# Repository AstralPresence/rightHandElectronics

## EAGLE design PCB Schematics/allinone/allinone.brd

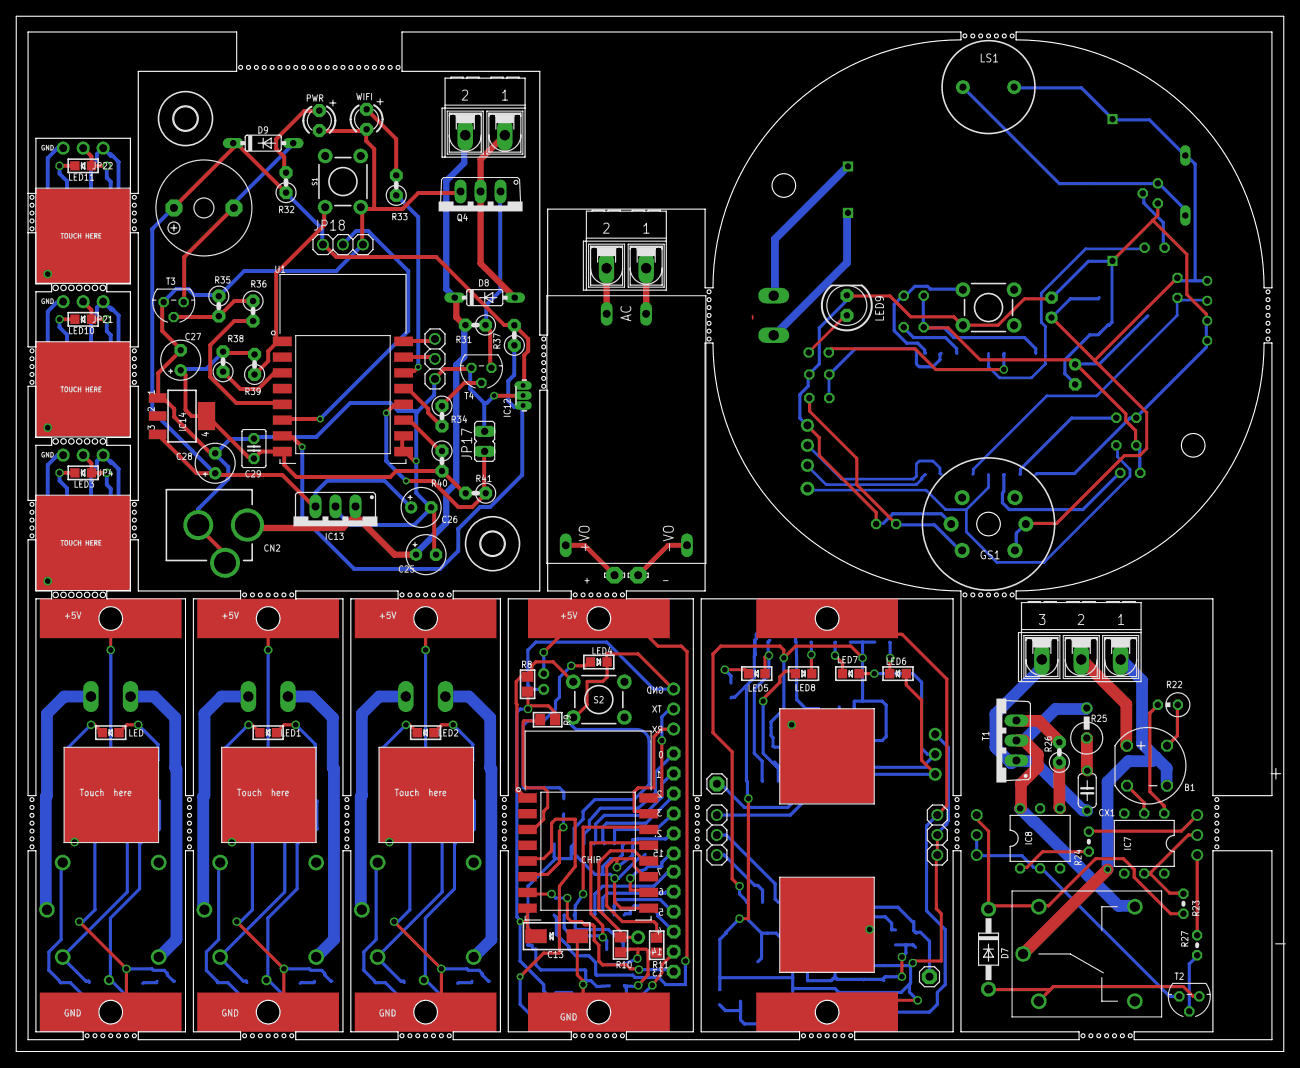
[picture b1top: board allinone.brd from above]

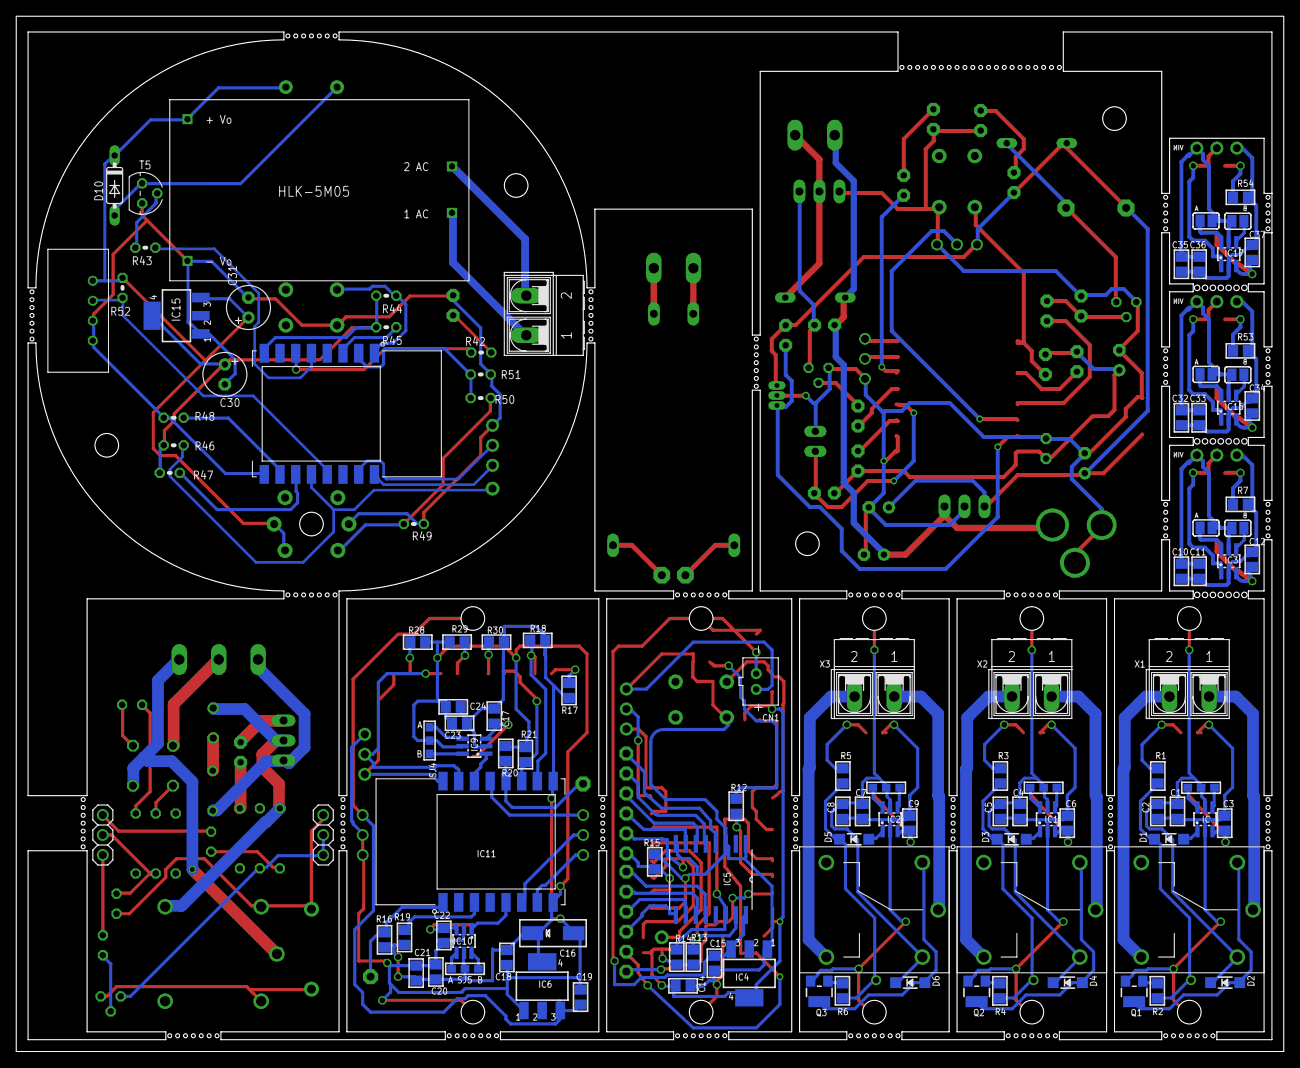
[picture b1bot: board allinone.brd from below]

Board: 2 copper layers, 161.0 x 131.5 mm, 224 parts (117 on the bottom side), 170 nets.

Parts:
AC: AK500/2-H
B1: W04/6/8/10; RB1A
C1, C4, C7, C10, C20, C23, C32, C35: 10uf; 0805
C2, C5, C8, C11, C21, C24, C33, C36: 0.1uf; 0805
C3, C6, C9, C17, C22: 50pF; 0805
C12, C34, C37: 50pf; 0805
C13, C16: 100UF; EIA6032-28/C-W
C14, C15: 0805
C18, C19: 10uF; 0805
C25, C26, C27, C28: E2,5-5
C29: C025-030X050
C30, C31: E2,5-6
CHIP: ESP-12E; XCVR_ESP8266-12E/ESP-12E
CN1: JST-PH-2-THM
CN2: DCJACK_2MM_PTH
CX1: C050-024X044
D1, D2, D3, D4, D5, D6: BAT54T1G; SOD-123
D7: 1N4004; DO41-10
D8, D9, D10: 1N4148DO35-7; DO35-7
DHT22: DHT22
GS1: GAS_SENSORMQ-3; GAS_SENSOR
IC, IC1, IC2, IC3, IC9, IC16, IC17: ttp223; BREAKOUT_SOT23-6
IC4: AMS1117; SOT223
IC5: PCF8574; SOIC127P1032X265-16N
IC6, IC15: ams117; SOT223
IC7: mct2e; DIL06
IC8: moc3051; DIL06
IC10: ttp23; BREAKOUT_SOT23-6
IC11: ESP8266-12E/ESP-12E; XCVR_ESP8266-12E/ESP-12E
IC12: A1202UA; SIP3-UA
IC13: 78XXS
IC14: 317EMP; SOT223
J1, J2, J3, J4, J5, J6: SOLDERJUMPER_REFLOW
JP1, JP2, JP3: 1X01_2MM
JP4, JP21, JP22: 1X03_ROUND
JP5, JP6: 1X06-CLEANBIG
JP7, JP20: 1X01-CLEANBIG
JP8, JP13, JP19: 1X03-CLEANBIG
JP9, JP10, JP11, JP12, JP16, JP18: 1X03
JP14, JP15: 1X01
JP17: JP1
LED, LED1, LED2, LED4, LED5, LED6, LED7, LED8: BLUE; CHIPLED_0805
LED3, LED10, LED11: blue; CHIPLED_0805
LED9: LED5MM
LS1: BUZZER-PTH; BUZZER-12MM
LSP1, LSP2: LSP10
M1, M2, M3: JQC3FC
MODULE: HLK-PM01
PAD, PAD1, PAD2, PAD3, PAD6, PAD7: pad; CAP_TOUCHPAD
PAD4: pad2; CAP_TOUCHPAD
PAD5: pad1; CAP_TOUCHPAD
PWR: LED3MM
Q1, Q2, Q3: 2N2222; SOT23-W
Q4: TO220V
R1, R2, R3, R4, R5, R6, R7, R53, R54: 1k; 0805
R8, R9: 12K; 0805
R10, R11, R15, R16, R18, R19, R20, R21: 12k; 0805
R12, R17, R28, R29: 220; 0805
R13, R14: 10K; 0805
R22: 180k; 0309V
R23, R49, R52: 10k; 0204V
R24: 100; 0204V
R25: 33; 0411V
R26: 330; 0207/2V
R27: 1k; 0204V
R30: 220\; 0805
R31, R35, R37, R38, R39, R40, R41: 10k; 0207/2V
R32: 200; 0207/2V
R33: 100; 0207/2V
R34, R36: 1k; 0207/2V
R42: 220; 0204V
R43: 330; 0204V
R44, R45, R46, R47, R48: 12k; 0204V
R50, R51: 0204V
RAIL1, RAIL3, RAIL5, RAIL7: RAIL1; STRIP
RAIL2, RAIL4, RAIL6, RAIL8: RAIL2; STRIP
S1: RST; TACTILE_SWITCH_PTH_6.0MM
S2, S3: MOMENTARY-SWITCH-SPST-PTH-6.0MM; TACTILE_SWITCH_PTH_6.0MM_KIT
SG1: F/TMB
SJ1, SJ2, SJ3, SJ4, SJ5: SOLDERJUMPER_2WAY_OPEN_0603
T1: BT138-V; TO220BV
T2, T3, T4, T5: BC547; TO92
U1, U2: ESP8266-12E/ESP-12E; XCVR_ESP8266-12E/ESP-12E
U$1: JQC3FC
U$2, U$3: STRIP
U$4, U$5: MOUNTINGHOLE_3.0
U$6: HLK-5M05
WIFI: LED3MM
X1, X2, X3, X4, X6: AK500/2-H
X5: AK500/3-H

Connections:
+: IC10.1, IC11.5
+3V1: C16.+, C18.1, C20.1, C21.1, C23.1, C24.1, IC6.4, IC9.5, IC10.5, IC11.8, R16.2, R19.2, R20.2, R21.2, R28.1, R29.1, SJ4.2, SJ5.2
+3V2: C27.+, C29.1, IC14.4, R38.2, R39.2, R40.2, R41.2, U1.8
+3V3: C13.+, C14.1, CHIP.8, IC4.4, R8.2, R9.2, R10.2, R11.2, R13.2, R14.2
+3V4: C30.+, IC15.4, R44.2, R45.2, R46.2, R47.2, U2.8
+5V: C1.1, C2.1, D2.C, IC.5, M1.+, RAIL1.STRIP, SJ2.2
+5V1: C4.1, C5.1, D4.C, IC1.5, M2.+, RAIL3.STRIP, SJ1.2
+5V2: C7.1, C8.1, D6.C, IC2.5, M3.+, RAIL5.STRIP, SJ3.2
+5V3: C10.1, C11.1, IC3.5, J1.1, J2.1, JP4.1
+5V4: C15.1, CN1.2, IC4.3, IC5.16, RAIL7.STRIP
+5V5: C19.1, IC6.3, JP12.1, U$2.STRIP
+5V6: C26.+, C28.+, D9.C, IC12.1, IC13.OUT, IC14.3, JP18.1, R32.1, R37.2, SG1.+
+5V7: C31.+, D10.C, DHT22.P$1, GS1.A1, GS1.HA, IC15.3, LS1.+, R52.2, U$6.4
+5V8: C32.1, C33.1, IC16.5, J3.1, J4.1, JP21.1
+5V9: C35.1, C36.1, IC17.5, J5.1, J6.1, JP22.1
+5V/1: LSP1.MP, MODULE.P$4
+5V/2: D7.C, JP10.3, R23.2, U$1.+
+12V: C25.+, CN2.PWR, D8.C, IC13.IN, R31.2, X6.2
-: IC9.1, IC11.20
AC1: M1.COM, X1.1
AC2: M1.NO, X1.2
AC3: M2.COM, X2.1
AC4: M2.NO, X2.2
AC5: M3.COM, X3.1
AC6: M3.NO, X3.2
ADC: R50.2, R51.1, U2.2
BUTTON: JP18.2, U1.6
BUZZER: R36.2, U1.5
FAN: CX1.2, T1.T1, X5.3
FIRING: JP9.3, R24.2
FLASH: IC11.18, JP15.1, R20.1
GND: C1.2, C2.2, C3.2, IC.2, LED.C, Q1.2, RAIL2.STRIP
GND1: C4.2, C5.2, C6.2, IC1.2, LED1.C, Q2.2, RAIL4.STRIP
GND2: C7.2, C8.2, C9.2, IC2.2, LED2.C, Q3.2, RAIL6.STRIP
GND3: C10.2, C11.2, C12.2, IC3.2, JP4.3, R7.2
GND4: C13.-, C14.2, C15.2, CHIP.15, CN1.1, IC4.1, IC5.1, IC5.3, IC5.8, JP8.3, LED4.C, R15.2, RAIL8.STRIP, S2.3
GND5: LSP2.MP, MODULE.P$3
GND6: C16.-, C17.2, C18.2, C19.2, C20.2, C21.2, C22.2, C23.2, C24.2, IC6.1, IC9.2, IC10.2, IC11.15, JP12.2, JP12.3, JP13.3, R17.1, R18.1, R30.1, U$3.STRIP
GND7: IC8.2, JP10.1, JP10.2, T2.1
GND8: C25.-, C26.-, C27.-, C28.-, C29.2, CN2.GND, CN2.GNDBREAK, IC12.2, IC13.GND, IC14.1, JP16.1, JP17.2, JP18.3, PWR.K, Q4.3, R35.1, S1.3, T3.1, T4.1, U1.15, U1.16, WIFI.K
GND9: C30.-, C31.-, DHT22.P$3, DHT22.P$4, GS1.HB, IC15.1, JP19.3, LED9.K, R48.1, R49.2, R51.2, S3.3, T5.1, U2.15, U$6.3
GND10: C32.2, C33.2, C34.2, IC16.2, JP21.3, R53.2
GND11: C35.2, C36.2, C37.2, IC17.2, JP22.3, R54.2
GPIO0: CHIP.18, JP7.1, R10.1
GPIO1: IC11.7, JP11.1
GPIO2: CHIP.17, JP5.2, R11.1
GPIO3: IC11.16, LED5.A, R18.2
GPIO4: IC11.17, LED8.A, R21.1
GPIO5: IC11.19, JP11.3
GPIO6: DHT22.P$2, R52.1, U2.19
GPIO7: JP20.1, R46.1, U2.18
GPIO8: R43.2, U2.5
GPIO9: R42.2, U2.6
GPIO12: IC11.6, JP11.2
GPIO13: CHIP.7, JP6.6
GPIO14: CHIP.5, JP6.5
GPIO15: CHIP.16, JP5.1, R15.1
HALL_SENSOR: IC12.3, R37.1, U1.7
HOT: B1.-, U$1.COM, X5.1
HOT1: IC8.6, R25.2, T1.T2, U$1.NO
LED: R33.1, U1.20
unnamed: LED.A, R1.2
unnamed: D1.A, IC.1
unnamed: C3.1, IC.3, PAD.P$1
unnamed: D2.A, M1._, Q1.3
unnamed: IC.6, SJ2.3
unnamed: IC.4, SJ2.1
unnamed: Q1.1, R2.1
unnamed: C6.1, IC1.3, PAD1.P$1
unnamed: IC1.6, SJ1.3
unnamed: IC1.4, SJ1.1
unnamed: D3.A, IC1.1
unnamed: D4.A, M2._, Q2.3
unnamed: Q2.1, R4.1
unnamed: LED1.A, R3.2
unnamed: C9.1, IC2.3, PAD2.P$1
unnamed: IC2.6, SJ3.3
unnamed: IC2.4, SJ3.1
unnamed: D5.A, IC2.1
unnamed: D6.A, M3._, Q3.3
unnamed: Q3.1, R6.1
unnamed: LED2.A, R5.2
unnamed: LED3.C, R7.1
unnamed: C12.1, IC3.3, PAD3.P$1
unnamed: IC3.6, J2.2
unnamed: IC3.4, J1.2
unnamed: CHIP.1, R8.1, S2.1
unnamed: CHIP.3, R9.1
unnamed: LED4.A, R12.1
unnamed: MODULE.P$1, X4.1
unnamed: MODULE.P$2, X4.2
unnamed: IC11.1, JP14.1, R16.1
unnamed: IC11.3, R19.1
unnamed: C22.1, IC10.3, PAD4.P$1
unnamed: IC10.6, SJ5.3
unnamed: IC10.4, SJ5.1
unnamed: C17.1, IC9.3, PAD5.P$1
unnamed: IC9.6, SJ4.3
unnamed: IC9.4, SJ4.1
unnamed: B1.AC1, R22.1
unnamed: B1.AC2, IC7.2
unnamed: IC7.1, R22.2
unnamed: IC8.1, R24.1
unnamed: IC8.4, R26.1
unnamed: R26.2, T1.G
unnamed: CX1.1, R25.1
unnamed: D7.A, T2.3, U$1._
unnamed: R27.1, T2.2
unnamed: LED5.C, R17.2
unnamed: LED6.C, R28.2
unnamed: LED7.C, R29.2
unnamed: LED8.C, R30.2
unnamed: Q4.1, R31.1, T4.3
unnamed: D8.A, Q4.2, X6.1
unnamed: D9.A, SG1.-, T3.3
unnamed: R35.2, R36.1, T3.2
unnamed: R34.1, T4.2
unnamed: R39.1, S1.1, U1.1
unnamed: R38.1, U1.3
unnamed: R40.1, U1.17
unnamed: JP17.1, R41.1, U1.18
unnamed: PWR.A, R32.2
unnamed: R33.2, WIFI.A
unnamed: GS1.B1, R49.1, R50.1
unnamed: LED9.A, R42.1
unnamed: D10.A, LS1.-, T5.3
unnamed: R44.1, S3.1, U2.1
unnamed: R45.1, U2.3
unnamed: R47.1, U2.17
unnamed: R48.2, U2.16
unnamed: R43.1, T5.2
unnamed: AC.1, U$6.2
unnamed: AC.2, U$6.1
unnamed: LED10.C, R53.1
unnamed: C34.1, IC16.3, PAD6.P$1
unnamed: IC16.6, J3.2
unnamed: IC16.4, J4.2
unnamed: LED11.C, R54.1
unnamed: C37.1, IC17.3, PAD7.P$1
unnamed: IC17.6, J5.2
unnamed: IC17.4, J6.2
NEUTRAL: B1.+, X5.2
O/P: D1.C, JP1.1, R1.1, R2.2
O/P1: D3.C, JP2.1, R3.1, R4.2
O/P2: D5.C, JP3.1, R5.1, R6.2
O/P3: IC3.1, JP4.2, LED3.A
O/P4: IC16.1, JP21.2, LED10.A
O/P5: IC17.1, JP22.2, LED11.A
P0: IC5.4, JP5.6
P1: IC5.5, JP5.5
P2: IC5.6, JP5.4
P3: IC5.7, JP5.3
P4: IC5.9, JP6.4
P5: IC5.10, JP6.3
P6: IC5.11, JP6.2
P7: IC5.12, JP6.1
RELAY: JP9.1, R27.2
RELAY1: R34.2, U1.19
RX: CHIP.21, JP8.1
RX1: IC11.21, JP13.2, LED7.A
RX2: JP16.2, U1.21
RX3: JP19.2, U2.21
SCL: CHIP.20, IC5.14, R14.1
SDA: CHIP.19, IC5.15, R13.1
TX: CHIP.22, JP8.2
TX1: IC11.22, JP13.1, LED6.A
TX2: JP16.3, U1.22
TX3: JP19.1, U2.22
WIFI: CHIP.6, R12.2
ZEROCROSSING: IC7.5, JP9.2, R23.1

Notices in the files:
parts and their libraries:
microbuilder: This work is placed in the public domain, and may be freely used for commercial and non-commercial work with the following conditions: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
SparkFun-Switches: Licensing: Creative Commons ShareAlike 4.0 International - https://creativecommons.org/licenses/by-sa/4.0
